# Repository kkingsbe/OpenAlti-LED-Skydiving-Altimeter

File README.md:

# OpenAlti-LED-Skydiving-Altimeter
This is an open-source version of the ColorAlti skydiving altimeter. This device features a barometric pressure sensing altimeter for determining altitude, 
and 3 2020-sized neopixels for relaying altitude information to the skydiver. This project is still early in its design phase, so this readme will be fleshed
out with much more information including build instructions eventually. This product will never be for sale, but the plans & firmware will always be free.

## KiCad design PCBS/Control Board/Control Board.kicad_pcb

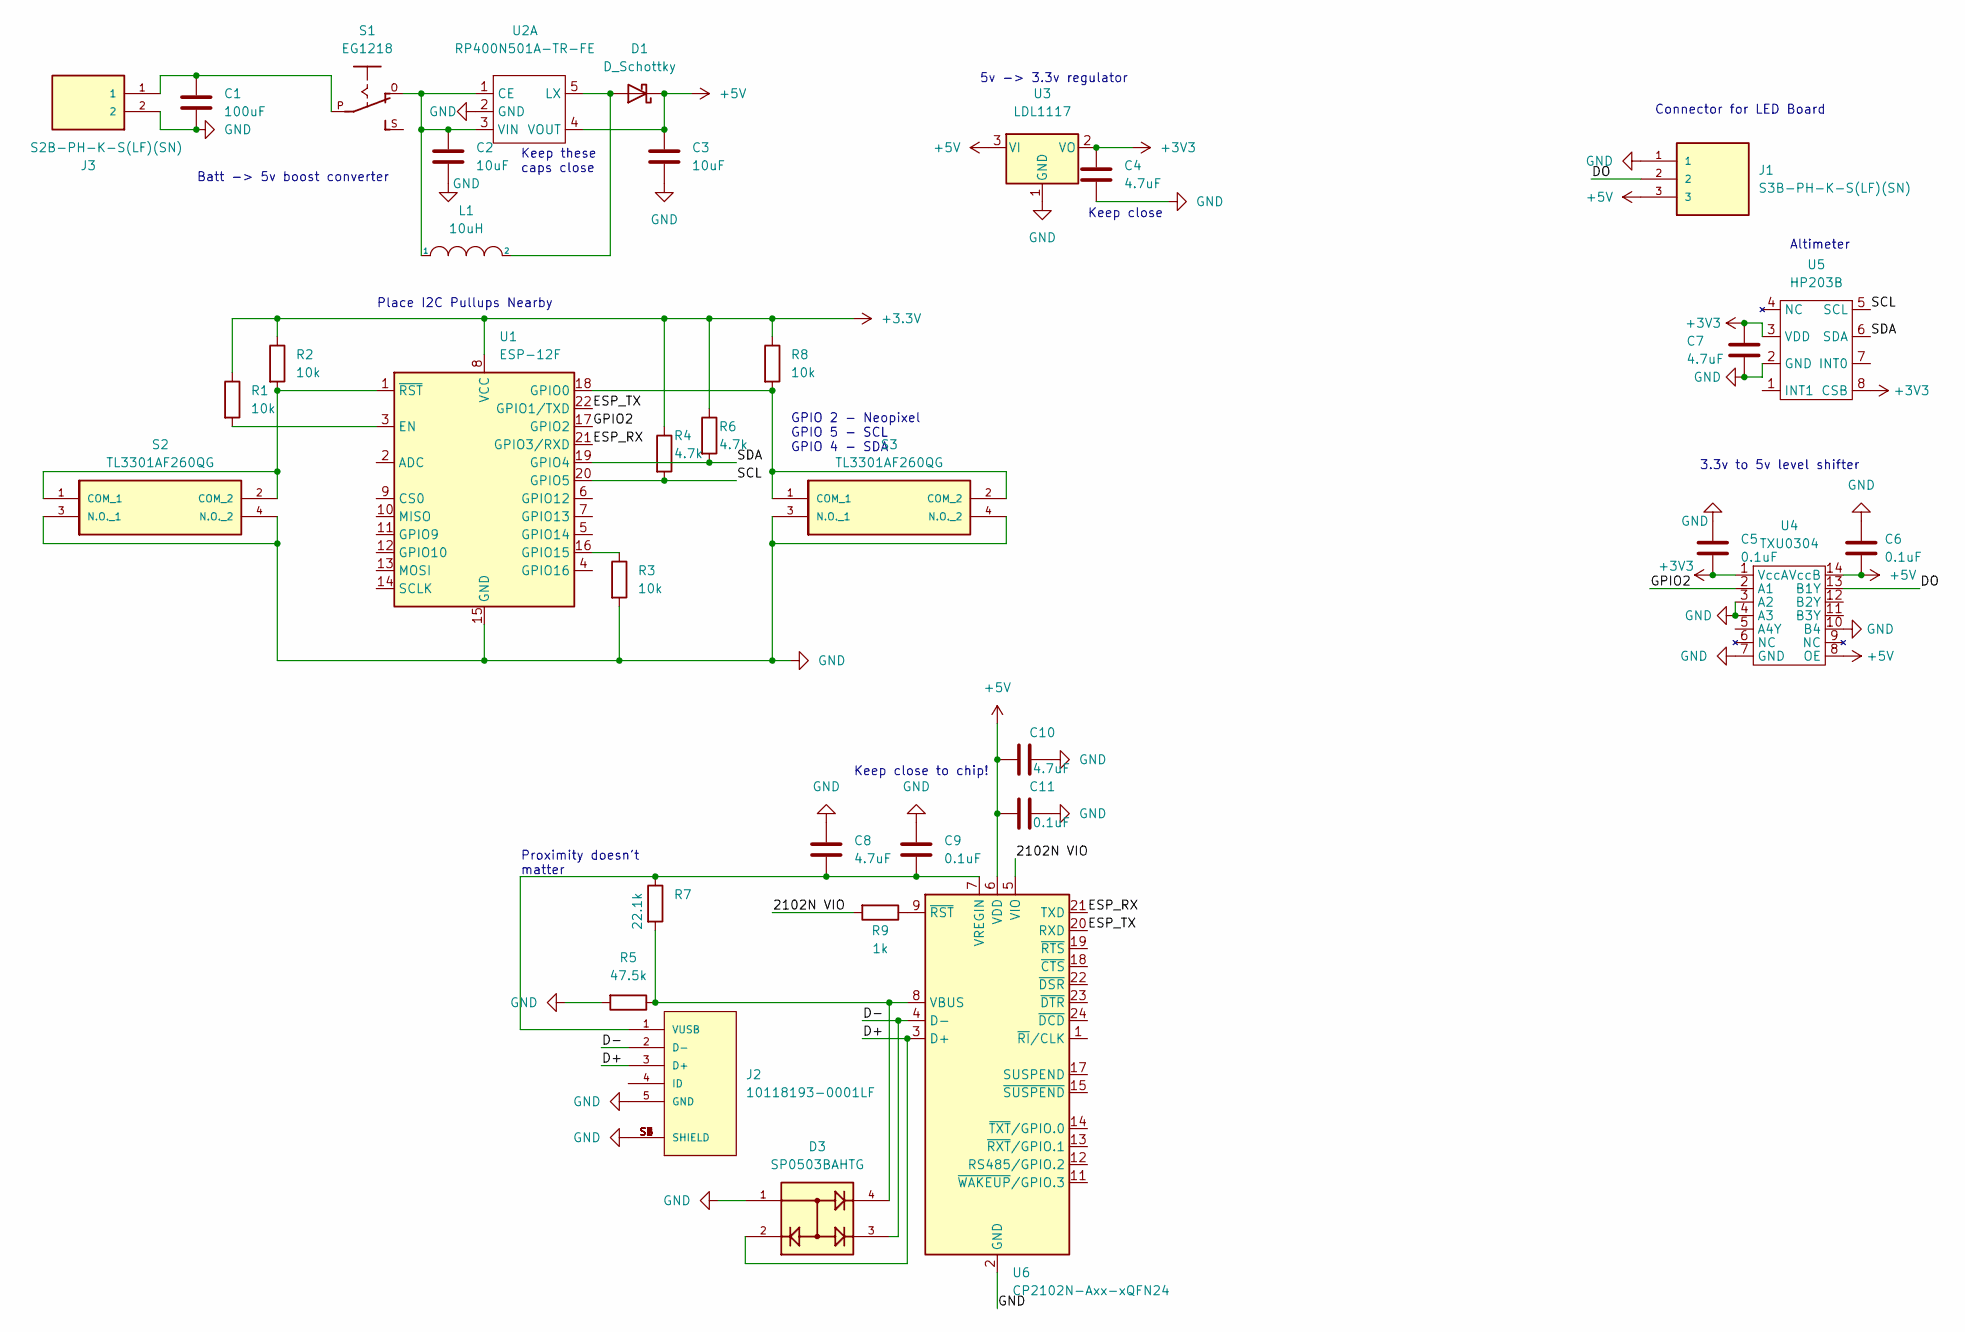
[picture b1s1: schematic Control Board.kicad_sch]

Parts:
C1: 100uF; C_1206_3216Metric
C2, C3: 10uF; C_0805_2012Metric
C4: 4.7uF; C_0805_2012Metric
C5, C6: 0.1uF; C_0402_1005Metric
C7: 4.7uF; C_0402_1005Metric
C8, C10: 4.7uF; C_0402_1005Metric; LCSC C129235
C9, C11: 0.1uF; C_0402_1005Metric; LCSC C325696
D1: D_Schottky; D_SOD-123
D3: SP0503BAHTG; SOT143; PARTREV N/A; LCSC C7074
J1: S3B-PH-K-S(LF)(SN); JST_S3B-PH-K-S(LF)(SN)
J2: 10118193-0001LF; FCI_10118193-0001LF
J3: S2B-PH-K-S(LF)(SN); JST_S2B-PH-K-S(LF)(SN)
L1: 10uH; IND_SLF7045T-100M1R3-PF
R1, R2, R3, R8: 10k; R_0402_1005Metric; LCSC C17414
R4, R6: 4.7k; R_0402_1005Metric; LCSC C17673
R5: 47.5k; R_0402_1005Metric; LCSC C23061
R7: 22.1k; R_0402_1005Metric; LCSC C325588
R9: 1k; R_0603_1608Metric; LCSC C21190
S1: EG1218
S2, S3: TL3301AF260QG; MANUFACTURER_PART_NUMBER TL3301AF260QG; MOUSER_PART_NUMBER 612-TL3301AF2
U1: ESP-12F; ESP-12E; LCSC C82891
U2: RP400N501A-TR-FE; SOT-23-5
U3: LDL1117; SOT-223-3_TabPin2
U4: TXU0304; TSSOP-14_4.4x5mm_P0.65mm
U5: HP203B
U6: CP2102N-Axx-xQFN24; QFN-24-1EP_4x4mm_P0.5mm_EP2.6x2.6mm; LCSC C969151

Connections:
+5V: C3.1, C6.2, C10.2, C11.2, D1.1 (K), J1.3, U2.4 (VOUT), U3.3 (VI), U4.8 (OE), U4.14 (VccB), U6.6 (VDD)
/2102N VIO: R9.2, U6.5 (VIO)
/D+: D3.2, J2.3 (D+), U6.3 (D+)
/D-: D3.3, J2.2 (D-), U6.4 (D-)
/DO: J1.2, U4.13 (B1Y)
/ESP_RX: U1.21 (GPIO3/RXD), U6.21 (TXD)
/ESP_TX: U1.22 (GPIO1/TXD), U6.20 (RXD)
/GPIO2: U1.17 (GPIO2), U4.2 (A1)
/SCL: R4.2, U1.20 (GPIO5), U5.5 (SCL)
/SDA: R6.2, U1.19 (GPIO4), U5.6 (SDA)
GND: C1.2, C2.2, C3.2, C4.2, C5.1, C6.1, C7.2, C8.1, C9.1, C10.1, C11.1, D3.1, J1.1, J2.5 (GND), J2.S1 (SHIELD), J2.S2 (SHIELD), J2.S3 (SHIELD), J2.S4 (SHIELD), J2.S5 (SHIELD), J2.S6 (SHIELD), J3.2, R3.2, R5.2, S2.3 (N.O._1), S2.4 (N.O._2), S3.3 (N.O._1), S3.4 (N.O._2), U1.15 (GND), U2.2 (GND), U3.1 (GND), U4.3 (A2), U4.4 (A3), U4.7 (GND), U4.10 (B4), U5.2 (GND), U6.2 (GND), U6.25 (GND)
unnamed: C1.1, J3.1, S1.P
unnamed: C2.1, L1.1, S1.O, U2.1 (CE), U2.3 (VIN)
unnamed: C8.2, C9.2, J2.1 (VUSB), R7.1, U6.7 (VREGIN)
unnamed: D1.2 (A), L1.2, U2.5 (LX)
unnamed: D3.4, R5.1, R7.2, U6.8 (VBUS)
unnamed: R1.2, U1.3 (EN)
unnamed: R2.2, S2.1 (COM_1), S2.2 (COM_2), U1.1 (~RST)
unnamed: R3.1, U1.16 (GPIO15)
unnamed: R8.2, S3.1 (COM_1), S3.2 (COM_2), U1.18 (GPIO0)
unnamed: R9.1, U6.9 (~RST)

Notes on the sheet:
Keep these caps close
Batt -> 5v boost converter
Keep close to chip!
Proximity doesn't matter
Keep close
Place I2C Pullups Nearby
Altimeter
3.3v to 5v level shifter
5v -> 3.3v regulator
GPIO 2 - Neopixel GPIO 5 - SCL GPIO 4 - SDA
Connector for LED Board

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
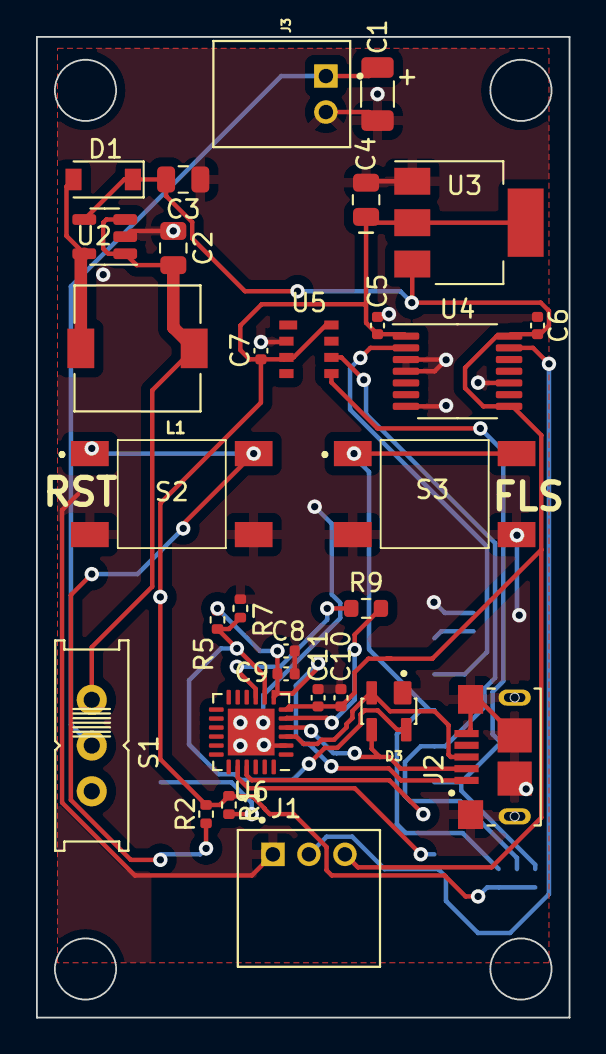
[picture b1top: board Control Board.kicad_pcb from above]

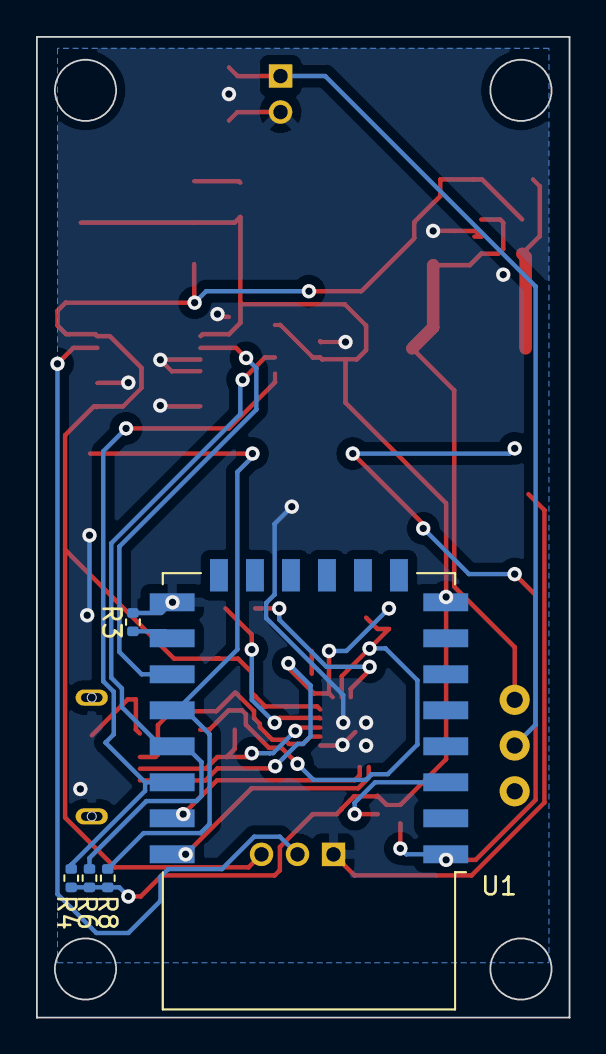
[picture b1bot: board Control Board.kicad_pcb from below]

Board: 2 copper layers, 29.6 x 54.5 mm, 35 parts (5 on the bottom side), 22 nets.

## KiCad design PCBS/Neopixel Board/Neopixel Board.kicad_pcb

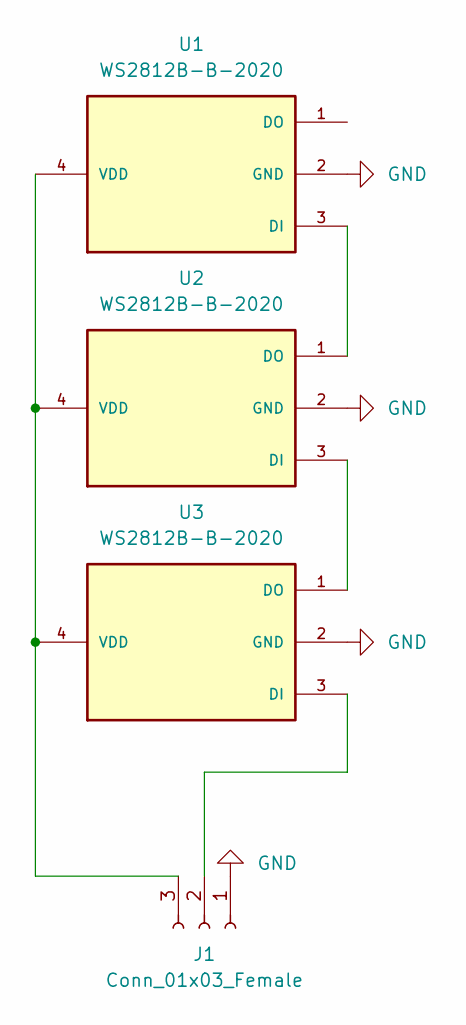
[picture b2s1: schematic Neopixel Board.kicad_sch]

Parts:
J1: Conn_01x03_Female; PinHeader_1x03_P2.54mm_Vertical
U1, U2, U3: WS2812B-B-2020; LED_WS2812B-2020; PARTREV 5

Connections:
GND: J1.1, U1.2 (GND), U2.2 (GND), U3.2 (GND)
unnamed: J1.2, U3.3 (DI)
unnamed: J1.3, U1.4 (VDD), U2.4 (VDD), U3.4 (VDD)
unnamed: U1.3 (DI), U2.1 (DO)
unnamed: U2.3 (DI), U3.1 (DO)

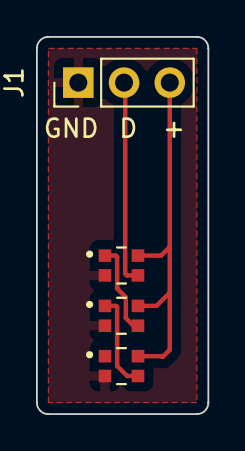
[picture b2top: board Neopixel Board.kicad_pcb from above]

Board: 2 copper layers, 9.5 x 21.0 mm, 4 parts (0 on the bottom side), 5 nets.

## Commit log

2022-10-04 First
2022-10-04 Updated schematic, started updating layout
2022-10-08 Completed switch to ESP-12F
